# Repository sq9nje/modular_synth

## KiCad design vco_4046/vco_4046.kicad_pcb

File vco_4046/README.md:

# 4046 VCO

A simple square wave VCO circuit based on the CMOS 4046 chip. Idea taken from the Modular in a Week Youtube series.

## References
* [Youtube video](https://www.youtube.com/watch?v=3ZLcbhSE1pc&list=PLyE56WXw0_5Q5QGMEXWmskuhojKyRdA3T&index=4)
* [Hackaday article](https://hackaday.com/2015/08/07/logic-noise-4046-voltage-controlled-oscillator-part-one/)

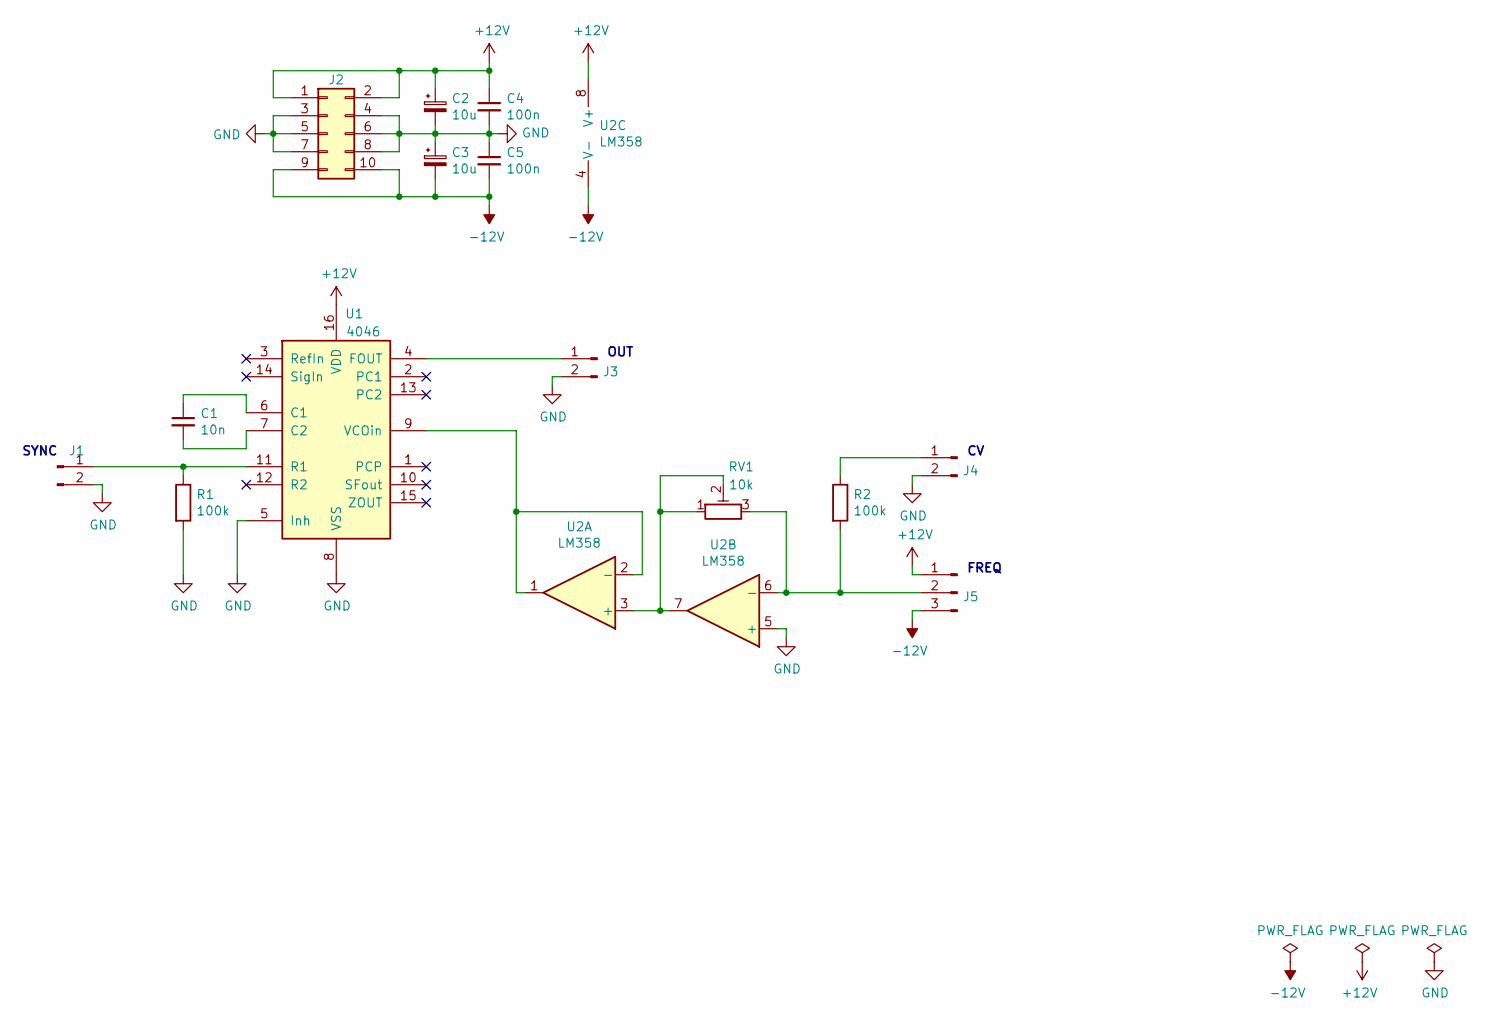
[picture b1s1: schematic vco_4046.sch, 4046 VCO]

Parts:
C1: 10n; C_Disc_D5.0mm_W2.5mm_P5.00mm
C2, C3: 10u; CP_Radial_D5.0mm_P2.00mm
C4, C5: 100n; C_Disc_D5.0mm_W2.5mm_P5.00mm
J1, J3, J4: Conn_01x02_Male; PinHeader_1x02_P2.54mm_Vertical
J2: Conn_02x05_Odd_Even; IDC-Header_2x05_P2.54mm_Vertical
J5: Conn_01x03_Male; PinHeader_1x03_P2.54mm_Vertical
R1, R2: 100k; R_Axial_DIN0207_L6.3mm_D2.5mm_P10.16mm_Horizontal
RV1: 10k; Potentiometer_ACP_CA9-V10_Vertical
U1: 4046; DIP-16_W7.62mm_LongPads
U2: LM358; DIP-8_W7.62mm_LongPads

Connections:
+12V: C2.1, C4.1, J2.1, J2.2, J5.1, U1.16 (VDD), U2.8 (V+)
-12V: C3.2, C5.2, J2.9, J2.10, J5.3, U2.4 (V-)
GND: C2.2, C3.1, C4.2, C5.1, J1.2, J2.3, J2.4, J2.5, J2.6, J2.7, J2.8, J3.2, J4.2, R1.2, U1.5 (Inh), U1.8 (VSS), U2.5 (+)
unnamed: C1.1, U1.6 (C1)
unnamed: C1.2, U1.7 (C2)
unnamed: J1.1, R1.1, U1.11 (R1)
unnamed: J3.1, U1.4 (FOUT)
unnamed: J4.1, R2.1
unnamed: J5.2, R2.2, RV1.3, U2.6 (-)
unnamed: RV1.1, RV1.2, U2.3 (+), U2.7
unnamed: U1.9 (VCOin), U2.1, U2.2 (-)

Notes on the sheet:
FREQ
SYNC
OUT

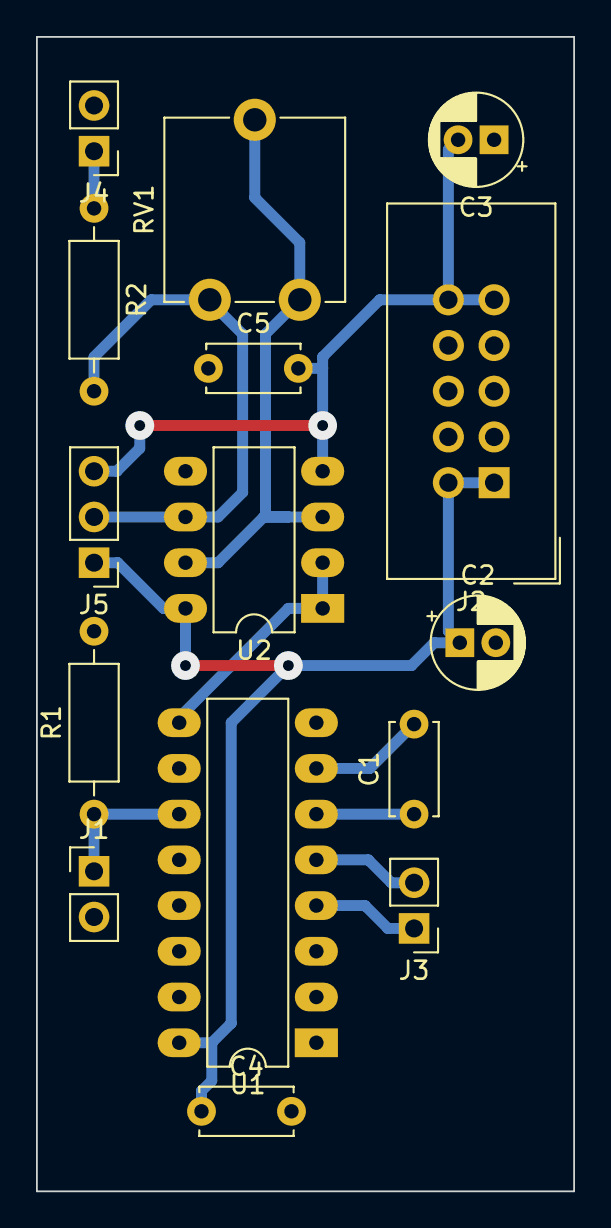
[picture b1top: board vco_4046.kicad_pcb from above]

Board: 2 copper layers, 29.8 x 64.1 mm, 15 parts (0 on the bottom side), 11 nets.

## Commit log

2020-03-01 4046 VCo schematics
2020-03-01 cleanup readme
2020-03-02 4046 VCO PCB
